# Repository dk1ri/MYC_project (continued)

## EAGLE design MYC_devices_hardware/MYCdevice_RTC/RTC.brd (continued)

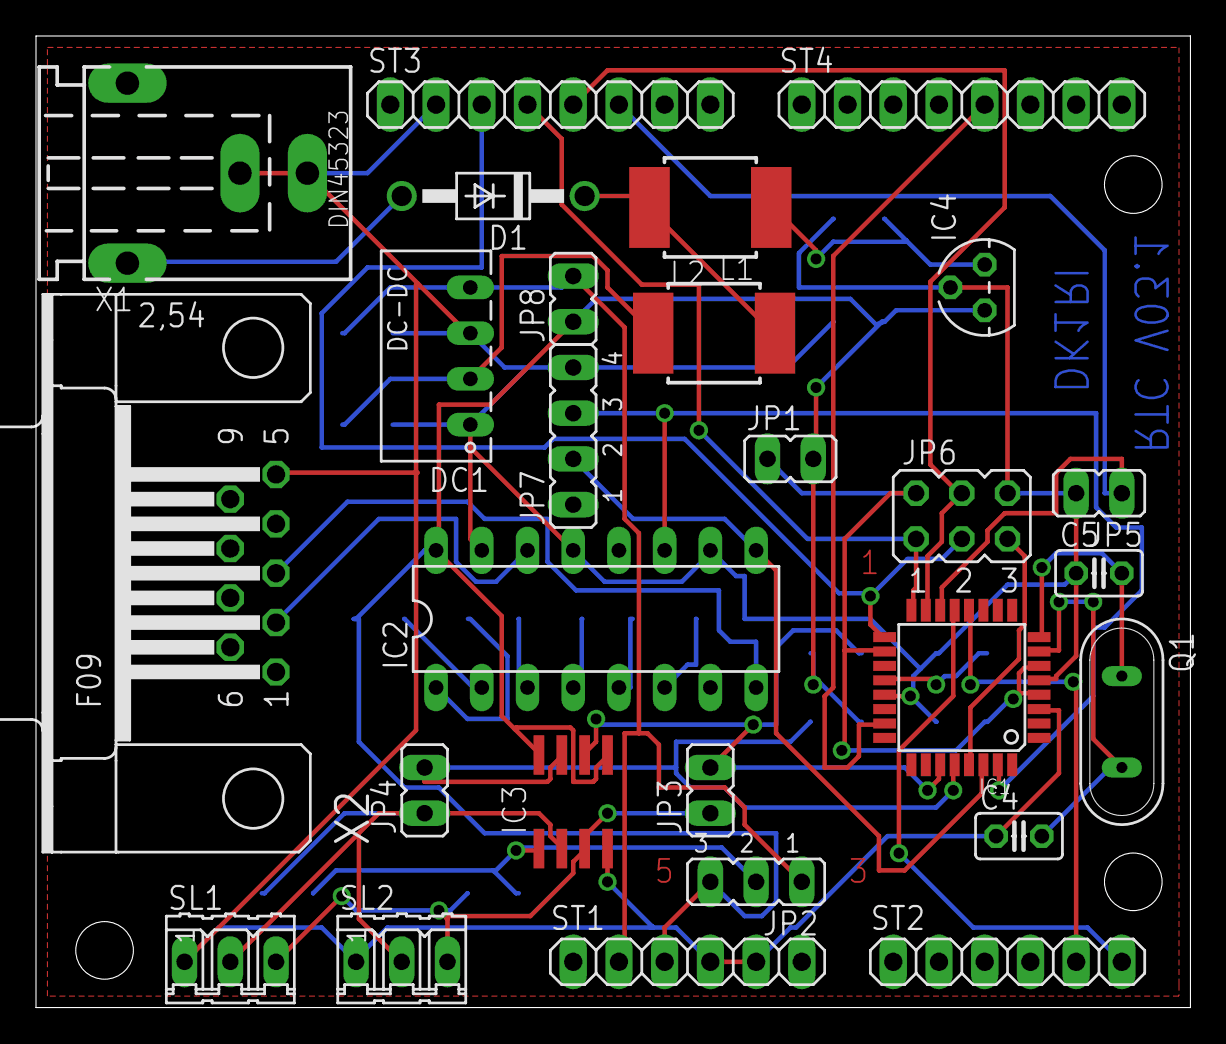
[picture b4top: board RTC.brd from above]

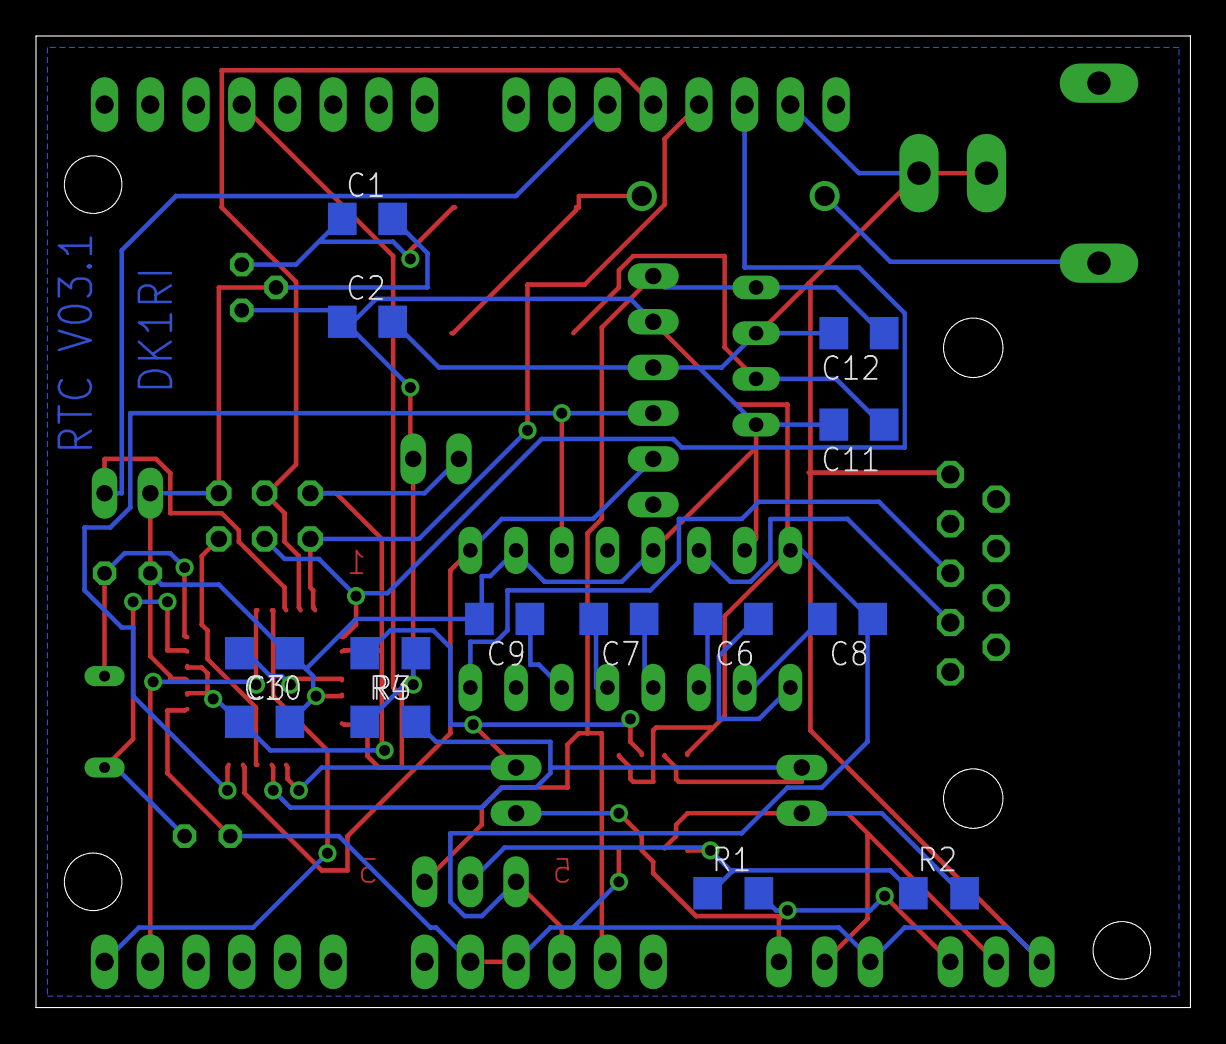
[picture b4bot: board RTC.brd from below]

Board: 2 copper layers, 64.1 x 54.0 mm, 41 parts (14 on the bottom side), 34 nets.

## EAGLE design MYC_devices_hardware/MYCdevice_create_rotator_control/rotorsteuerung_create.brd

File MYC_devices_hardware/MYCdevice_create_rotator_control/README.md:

# MYC Interface a Create RC5A Rotator

This is a device, which understand the MYC protocol via I2C and control a antenna rotator.

The board is designed to fit into the control box

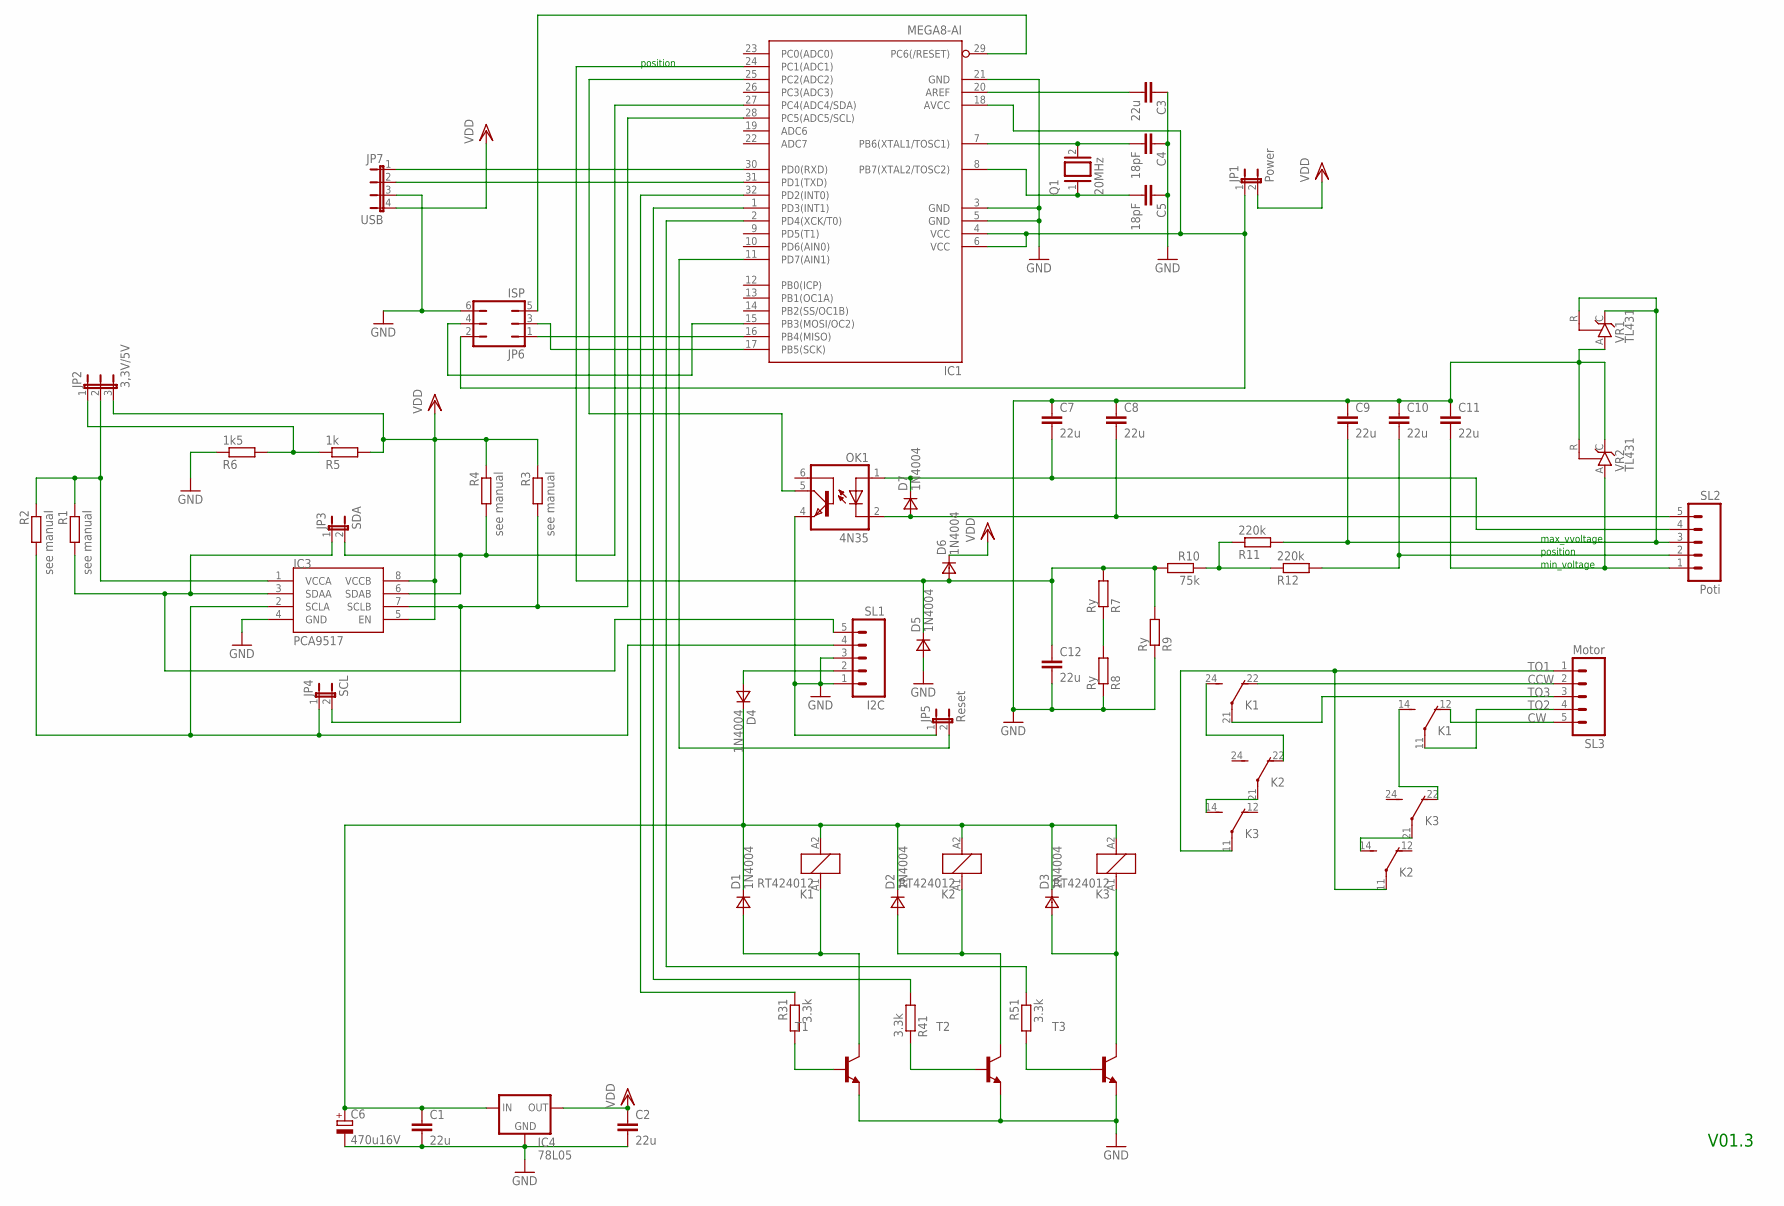
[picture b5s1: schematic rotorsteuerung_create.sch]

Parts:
C1, C2, C3, C7, C8, C9, C10, C11, C12: 22u; C1206
C4, C5: 18pF; C025-024X044
C6: 470u16V; E5-10,5
D1, D2, D3, D4, D5, D6, D7: 1N4004; E2LINE
IC1: MEGA8-AI; TQFP32-08
IC3: PCA9517; SO-08
IC4: 78L05; 78LXX
JP1: Power; JP1
JP2: 3,3V/5V; JP2
JP3: SDA; JP1
JP4: SCL; JP1
JP5: Reset; JP1
JP6: ISP; JP3Q
JP7: USB; JP4
K1, K2, K3: RT424012; RT2C/O
OK1: 4N35; DIL06
Q1: 20MHz; QS
R1, R2: see manual; M1206
R3, R4: see manual; R1206
R5: 1k; R1206
R6: 1k5; R1206
R7, R8, R9: Ry; 0204/7
R10: 75k; 0204/7
R11, R12: 220k; 0204/7
R31, R41, R51: 3.3k; R1206
SL1: I2C; 05P
SL2: Poti; 05P
SL3: Motor; 05P
T1, T2, T3: BC817-16-NPN-SOT23-BEC; SOT23-BEC
VR1, VR2: TL431; TO92-CLP

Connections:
C7: C7.2, D7.1 (C), OK1.1 (A), SL2.4
C9: C9.2, R11.2, SL2.3, VR1.C, VR1.R
CCW: K1.22 (O), SL3.2
CW: K1.12 (O), SL3.5
GND: C1.2, C2.2, C3.1, C4.1, C5.1, C6.-, C7.1, C8.1, C9.1, C10.1, C11.1, C12.2, D5.2 (A), IC1.3 (GND), IC1.5 (GND), IC1.21 (GND), IC3.4 (GND), IC4.GND, JP5.1, JP6.6, JP7.3, OK1.4 (EMI), R6.1, R8.1, R9.1, SL1.1, SL1.3, T1.E, T2.E, T3.E, VR1.A, VR2.C, VR2.R
unnamed: IC1.27 (PC4(ADC4/SDA)), IC3.6 (SDAB), JP3.2, R4.2
unnamed: C8.2, D7.2 (A), OK1.2 (C), SL2.5
unnamed: C11.2, SL2.1, VR2.A
unnamed: D4.2 (A), SL1.2
unnamed: K1.24 (S), K2.22 (O)
unnamed: R7.1, R8.2
unnamed: IC1.16 (PB4(MISO)), JP6.1
unnamed: K1.14 (S), K3.22 (O)
unnamed: R10.1, R11.1, R12.1
unnamed: IC1.4 (VCC), IC1.6 (VCC), IC1.18 (AVCC), JP1.1, JP6.2
unnamed: K2.21, K3.14 (S)
unnamed: R41.1, T2.B
unnamed: IC1.2 (PD4(XCK/T0)), R51.1
unnamed: K2.14 (S), K3.21
unnamed: C12.1, D5.1 (C), D6.2 (A), IC1.24 (PC1(ADC1)), R7.2, R9.2, R10.2
unnamed: JP2.1, R5.1, R6.2
unnamed: C4.2, IC1.7 (PB6(XTAL1/TOSC1)), Q1.2
unnamed: IC1.17 (PB5(SCK)), JP6.3
unnamed: IC1.1 (PD3(INT1)), R41.2
unnamed: IC1.25 (PC2(ADC2)), OK1.5 (COL)
unnamed: IC3.3 (SDAA), JP3.1, R1.2, SL1.5
unnamed: C1.1, C6.+, D1.1 (C), D2.1 (C), D3.1 (C), D4.1 (C), IC4.IN, K1.A2 (2), K2.A2 (2), K3.A2 (2)
unnamed: IC1.11 (PD7(AIN1)), JP5.2
unnamed: IC3.2 (SCLA), JP4.1, R2.2, SL1.4
unnamed: C10.2, R12.2, SL2.2
unnamed: IC3.1 (VCCA), JP2.2, R1.1, R2.1
unnamed: IC1.30 (PD0(RXD)), JP7.1
unnamed: IC1.15 (PB3(MOSI/OC2)), JP6.4
unnamed: IC1.31 (PD1(TXD)), JP7.2
unnamed: IC1.32 (PD2(INT0)), R31.1
unnamed: R31.2, T1.B
unnamed: C3.2, IC1.20 (AREF)
unnamed: R51.2, T3.B
unnamed: C5.2, IC1.8 (PB7(XTAL2/TOSC2)), Q1.1
unnamed: IC1.29 (PC6(/RESET)), JP6.5
unnamed: D1.2 (A), K1.A1 (1), T1.C
unnamed: D2.2 (A), K2.A1 (1), T2.C
unnamed: D3.2 (A), K3.A1 (1), T3.C
unnamed: IC1.28 (PC5(ADC5/SCL)), IC3.7 (SCLB), JP4.2, R3.2
TO1: K2.11, K3.11, SL3.1
TO2: K1.11, SL3.4
TO3: K1.21, SL3.3
VDD: C2.1, D6.1 (C), IC3.5 (EN), IC3.8 (VCCB), IC4.OUT, JP1.2, JP2.3, JP7.4, R3.1, R4.1, R5.2

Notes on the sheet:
V01.3
max_vvoltage
min_voltage
position

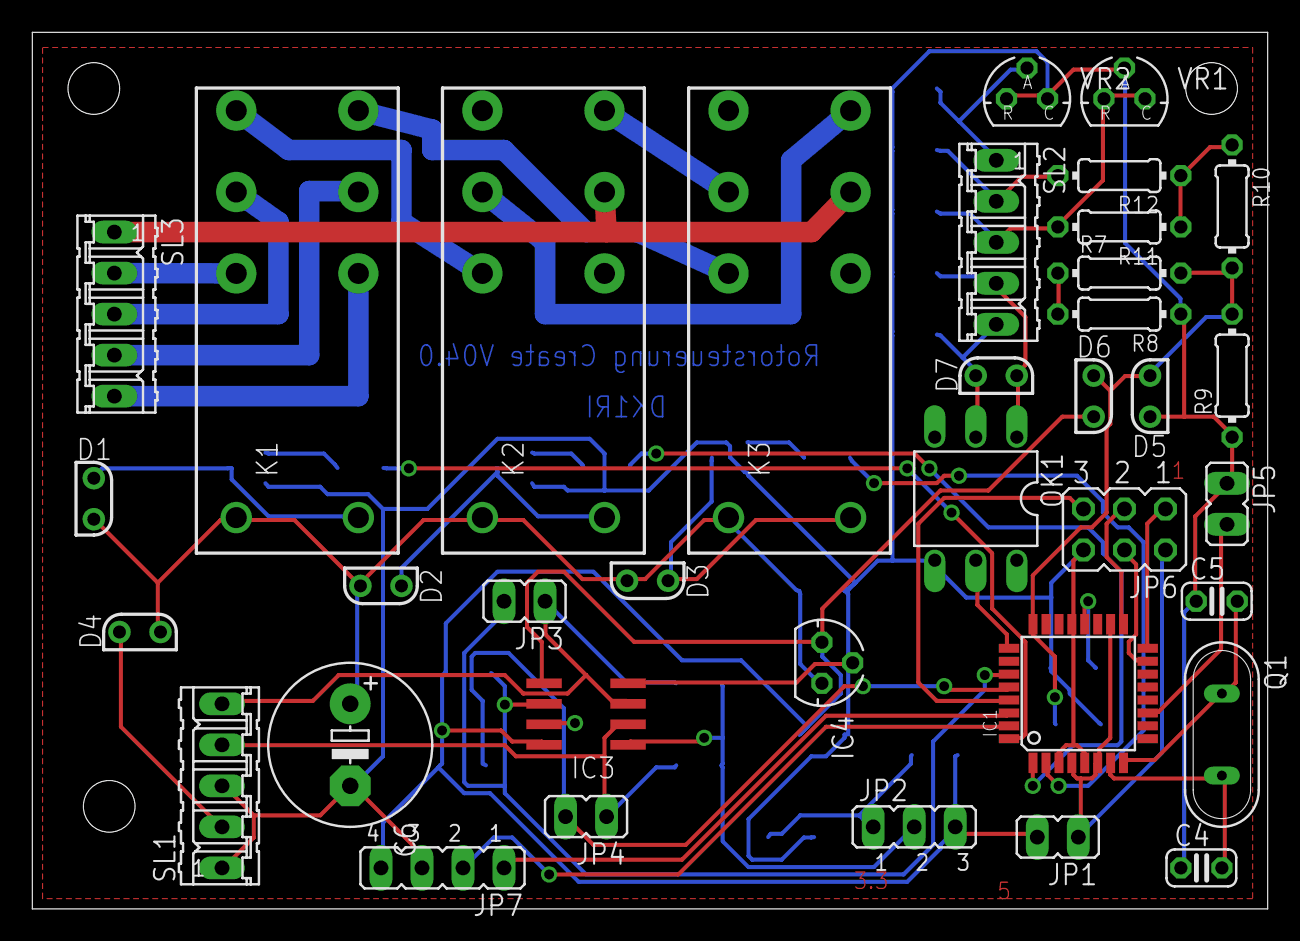
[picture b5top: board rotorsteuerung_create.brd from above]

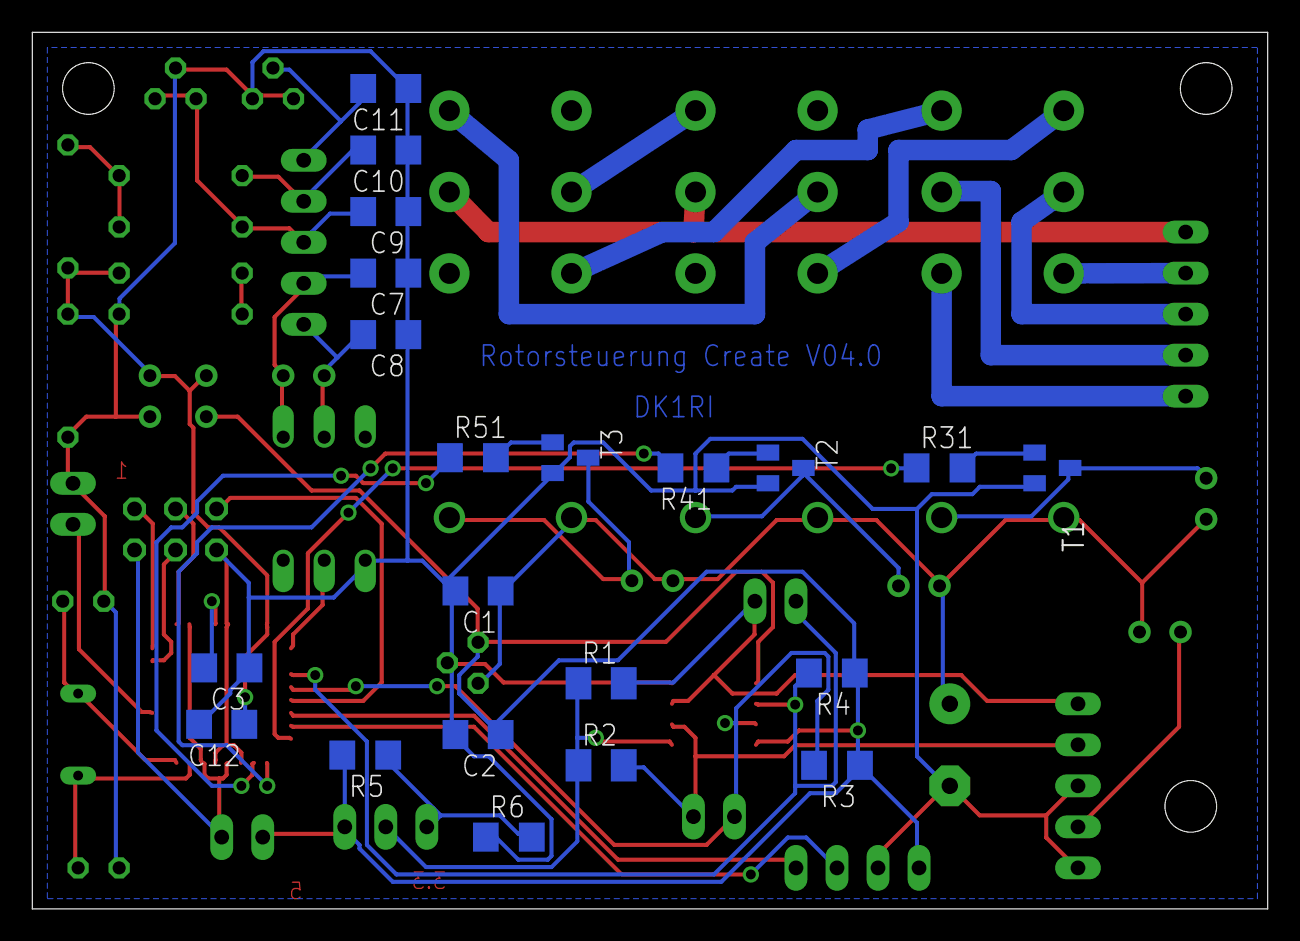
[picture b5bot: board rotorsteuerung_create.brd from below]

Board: 2 copper layers, 76.5 x 54.3 mm, 57 parts (21 on the bottom side), 48 nets.

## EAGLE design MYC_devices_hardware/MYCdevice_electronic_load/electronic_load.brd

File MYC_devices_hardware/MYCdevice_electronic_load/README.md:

# MYC electronic load
This is a device, which understand the MYC protocol via I2C or RS232/USB and works as a resistor, which can handle 90V, 210A or 350W (with 7 FETS IRFP150)

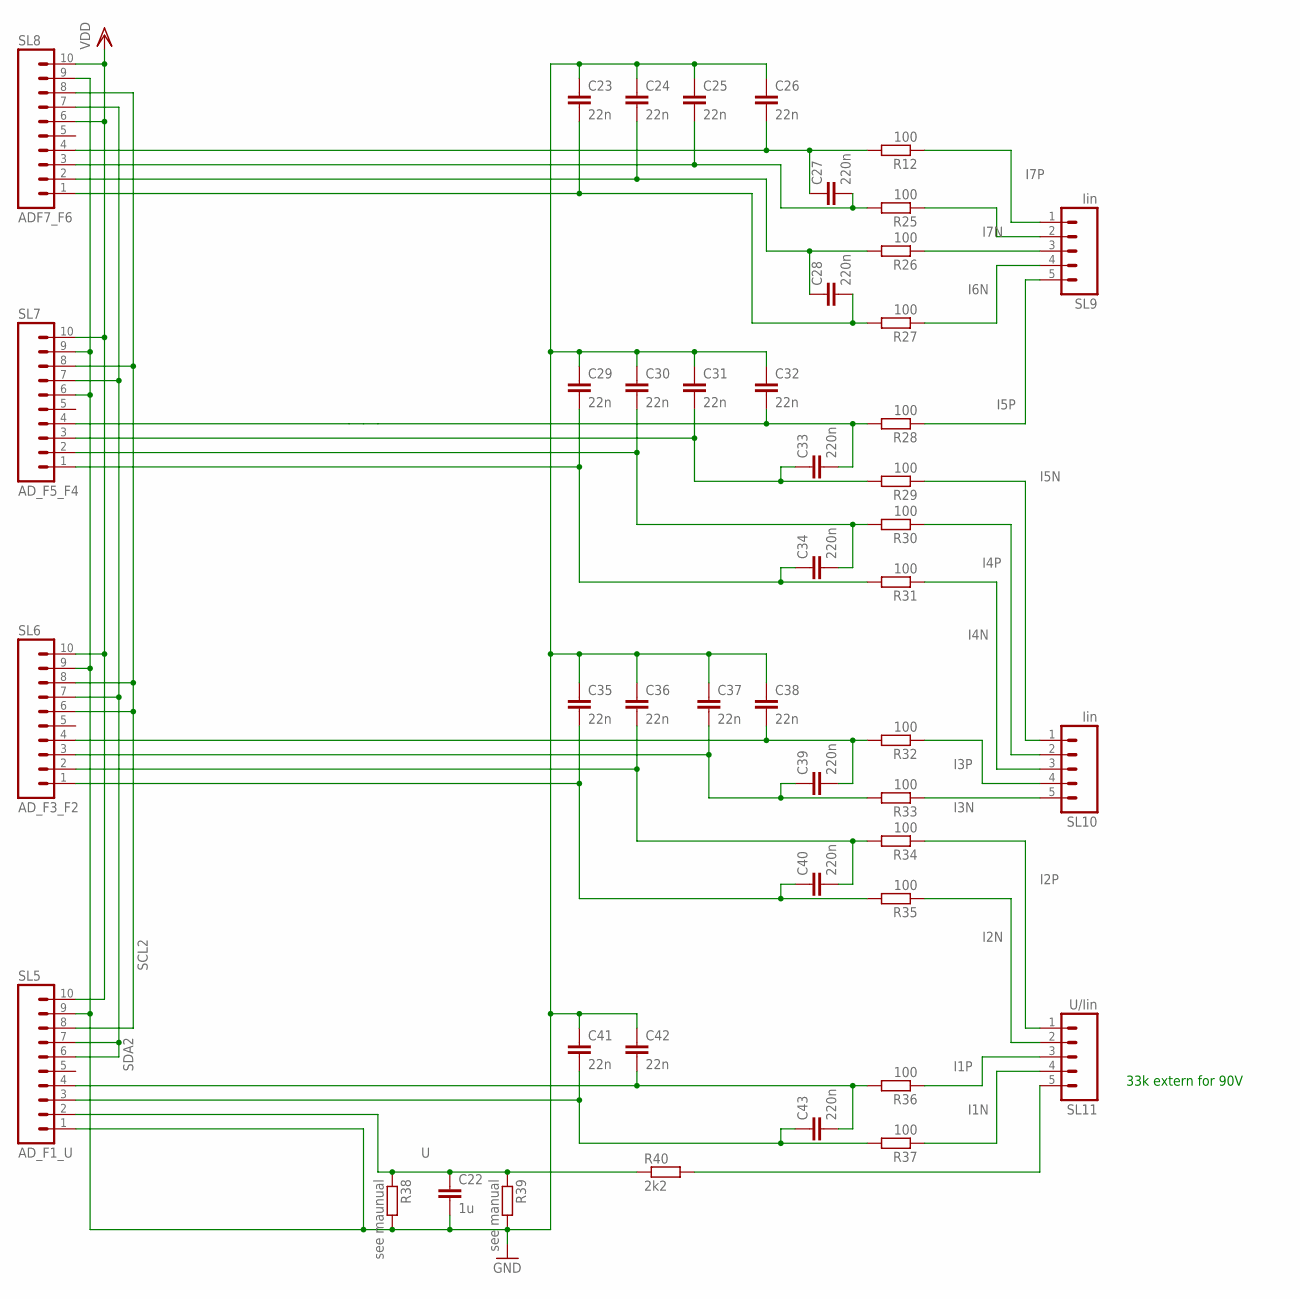
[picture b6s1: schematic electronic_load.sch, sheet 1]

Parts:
C22: 1u; C1206
C23, C24, C25, C26, C29, C30, C31, C32, C35, C36, C37, C38, C41, C42: 22n; C1206
C27, C28, C33, C34, C39, C40, C43: 220n; C1206
R12, R25, R26, R27, R28, R29, R30, R31, R32, R33, R34, R35, R36, R37: 100; R1206
R38: see maunual; R1206
R39: see manual; R1206
R40: 2k2; R1206
SL5: AD_F1_U; 10P
SL6: AD_F3_F2; 10P
SL7: AD_F5_F4; 10P
SL8: ADF7_F6; 10P
SL9, SL10: Iin; 05P
SL11: U/Iin; 05P

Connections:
GND: C22.2, C23.1, C24.1, C25.1, C26.1, C29.1, C30.1, C31.1, C32.1, C35.1, C36.1, C37.1, C38.1, C41.1, C42.1, R38.2, R39.2, SL5.1, SL5.9, SL6.9, SL7.6, SL7.9, SL8.9; also elsewhere on the board
I1N: R37.1, SL11.4
I1P: R36.1, SL11.3
I2N: R35.1, SL11.2
I2P: R34.1, SL11.1
I3N: R33.1, SL10.5
I3P: R32.1, SL10.4
I4N: R31.1, SL10.3
I4P: R30.1, SL10.2
I5N: R29.1, SL10.1
I5P: R28.1, SL9.5
I6N: R27.1, SL9.4
I6P: R26.1, SL9.3
I7N: R25.1, SL9.2
I7P: R12.1, SL9.1
unnamed: C26.2, C27.1, R12.2, SL8.4
unnamed: C32.2, C33.2, R28.2, SL7.4
unnamed: R40.2, SL11.5
unnamed: C31.2, C33.1, R29.2, SL7.3
unnamed: C30.2, C34.2, R30.2, SL7.2
unnamed: C29.2, C34.1, R31.2, SL7.1
unnamed: C38.2, C39.2, R32.2, SL6.4
unnamed: C37.2, C39.1, R33.2, SL6.3
unnamed: C36.2, C40.2, R34.2, SL6.2
unnamed: C24.2, C28.1, R26.2, SL8.2
unnamed: C25.2, C27.2, R25.2, SL8.3
unnamed: C35.2, C40.1, R35.2, SL6.1
unnamed: C23.2, C28.2, R27.2, SL8.1
unnamed: C42.2, C43.2, R36.2, SL5.4
unnamed: C41.2, C43.1, R37.2, SL5.3
SCL2: SL5.8, SL6.6, SL6.8, SL7.8, SL8.8; also elsewhere on the board
SDA2: SL5.6, SL5.7, SL6.7, SL7.7, SL8.7; also elsewhere on the board
U: C22.1, R38.1, R39.1, R40.1, SL5.2
VDD: SL5.10, SL6.10, SL7.10, SL8.6, SL8.10; also elsewhere on the board

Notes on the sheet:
33k extern for 90V

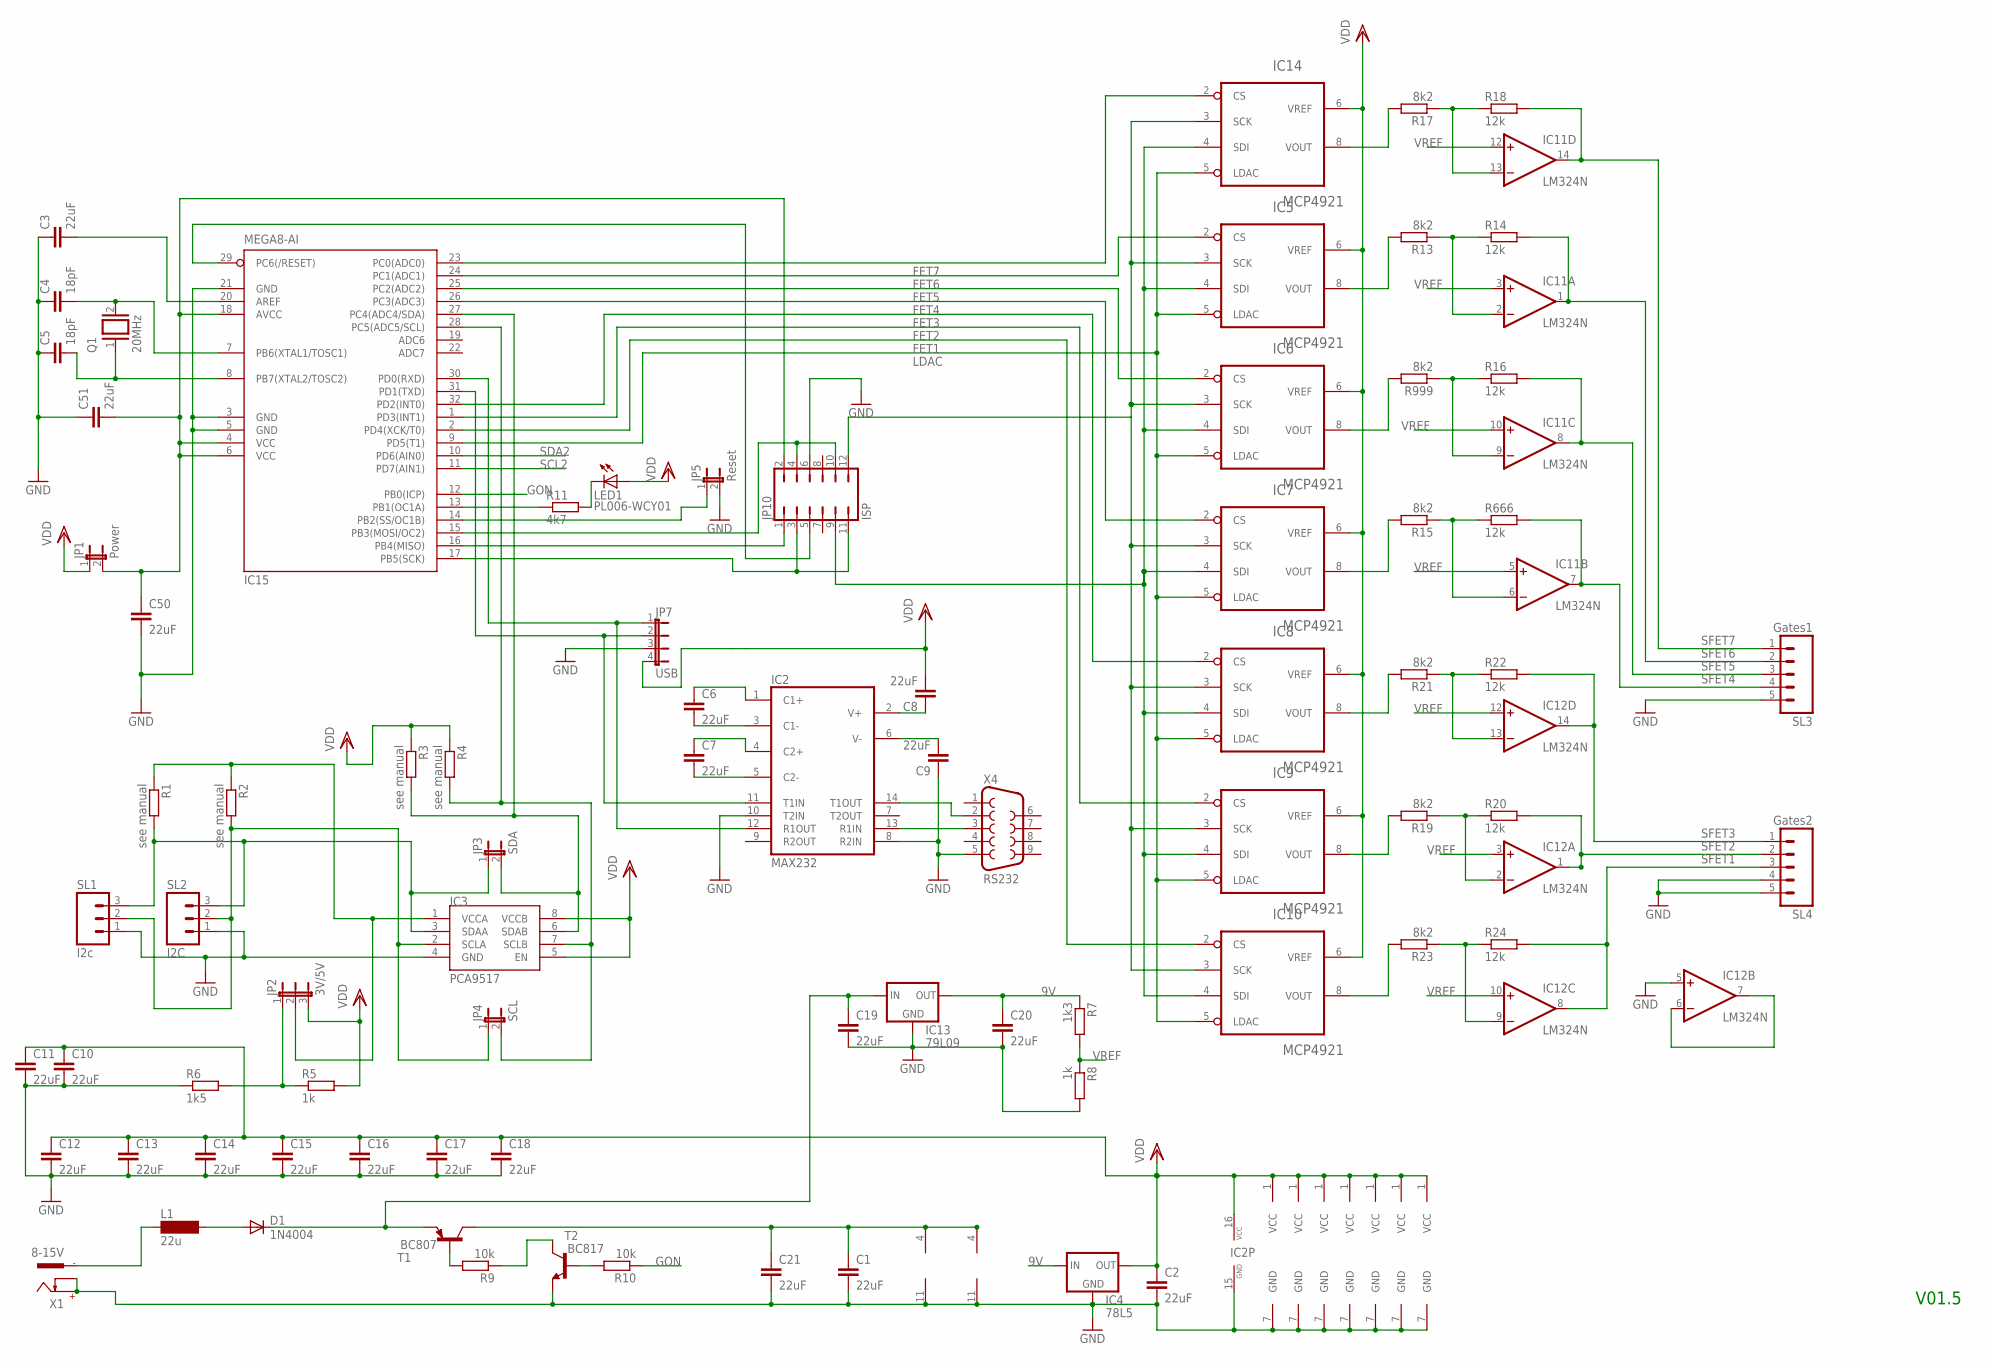
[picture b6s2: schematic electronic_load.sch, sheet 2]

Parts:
C1, C2, C3, C6, C7, C8, C9, C10, C11, C12, C13, C14, C15, C16, C17, C18, C19, C20, C21, C50, C51: 22uF; C1206
C4, C5: 18pF; C025-025X050
D1: 1N4004; DO41-10
IC2: MAX232; DIL16
IC3: PCA9517; SO-08
IC4: 78L5; 78LXX
IC5, IC6, IC7, IC8, IC9, IC10, IC14: MCP4921; DIL08
IC11, IC12: LM324N; DIL14
IC13: 79L09; 78LXX
IC15: MEGA8-AI; TQFP32-08
JP1: Power; JP1
JP2: 3V/5V; JP2
JP3: SDA; JP1
JP4: SCL; JP1
JP5: Reset; JP1
JP7: USB; JP4
JP10: ISP; JP6Q
L1: 22u; MS85
LED1: PL006-WCY01; SOT23
Q1: 20MHz; QS
R1, R2, R3, R4: see manual; R1206
R5, R8: 1k; R1206
R6: 1k5; R1206
R7: 1k3; R1206
R9, R10: 10k; R1206
R11: 4k7; R1206
R13, R15, R17, R19, R21, R23, R999: 8k2; R1206
R14, R16, R18, R20, R22, R24, R666: 12k; R1206
SL1: I2c; 03P
SL2: I2C; 03P
SL3: Gates1; 05P
SL4: Gates2; 05P
T1: BC807; SOT23-BEC
T2: BC817; SOT23-BEC
X1: 8-15V; 737992-5
X4: RS232; F09H

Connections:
9V: C20.1, IC4.IN, IC13.OUT, R7.1
C13: C6.1, IC2.1 (C1+)
FET1: IC10.2 (CS), IC15.2 (PD4(XCK/T0))
FET2: IC9.2 (CS), IC15.1 (PD3(INT1))
FET3: IC8.2 (CS), IC15.32 (PD2(INT0))
FET4: IC7.2 (CS), IC15.26 (PC3(ADC3))
FET5: IC6.2 (CS), IC15.25 (PC2(ADC2))
FET6: IC5.2 (CS), IC15.24 (PC1(ADC1))
FET7: IC14.2 (CS), IC15.23 (PC0(ADC0))
GND: C1.2, C2.2, C3.1, C4.1, C5.1, C9.1, C10.2, C11.2, C12.2, C13.2, C14.2, C15.2, C16.2, C17.2, C18.2, C19.2, C20.2, C21.2, C50.2, C51.1, IC2.8 (R2IN), IC2.10 (T2IN), IC2.15 (GND), IC3.4 (GND), IC4.GND, IC5.7 (GND), IC6.7 (GND), IC7.7 (GND), IC8.7 (GND), IC9.7 (GND), IC10.7 (GND), IC11.11 (V-), IC12.5 (+IN), IC12.11 (V-), IC13.GND, IC14.7 (GND), IC15.3 (GND), IC15.5 (GND), IC15.21 (GND), JP5.2, JP7.3, JP10.6, R6.1, R8.2, SL1.1, SL2.1, SL3.5, SL4.4, SL4.5, T2.E, X1.+, X1.K, X4.5; also elsewhere on the board
GON: IC15.12 (PB0(ICP)), R10.1
LDAC: IC5.5 (LDAC), IC6.5 (LDAC), IC7.5 (LDAC), IC8.5 (LDAC), IC9.5 (LDAC), IC10.5 (LDAC), IC14.5 (LDAC), IC15.9 (PD5(T1))
unnamed: C7.2, IC2.5 (C2-)
unnamed: C50.1, C51.2, IC15.4 (VCC), IC15.6 (VCC), IC15.18 (AVCC), JP1.2, JP10.2
unnamed: IC3.3 (SDAA), JP3.1, R1.2, SL1.3, SL2.3
unnamed: IC2.11 (T1IN), IC15.31 (PD1(TXD)), JP7.2
unnamed: L1.1, X1.-1
unnamed: IC2.13 (R1IN), X4.3
unnamed: IC6.8 (VOUT), R999.2
unnamed: C5.2, IC15.8 (PB7(XTAL2/TOSC2)), Q1.1
unnamed: D1.A, L1.2
unnamed: C7.1, IC2.4 (C2+)
unnamed: C6.2, IC2.3 (C1-)
unnamed: IC15.16 (PB4(MISO)), JP10.1
unnamed: C8.1, IC2.2 (V+)
unnamed: C9.2, IC2.6 (V-)
unnamed: IC15.29 (PC6(/RESET)), JP10.5
unnamed: C4.2, IC15.7 (PB6(XTAL1/TOSC1)), Q1.2
unnamed: IC5.4 (SDI), IC6.4 (SDI), IC7.4 (SDI), IC8.4 (SDI), IC9.4 (SDI), IC10.4 (SDI), IC14.4 (SDI), JP10.9
unnamed: IC14.8 (VOUT), R17.2
unnamed: IC3.2 (SCLA), JP4.1, R2.2, SL1.2, SL2.2
unnamed: IC15.15 (PB3(MOSI/OC2)), JP10.4, JP10.10
unnamed: IC9.8 (VOUT), R19.2
unnamed: IC8.8 (VOUT), R21.2
unnamed: IC5.3 (SCK), IC6.3 (SCK), IC7.3 (SCK), IC8.3 (SCK), IC9.3 (SCK), IC10.3 (SCK), IC14.3 (SCK), JP10.12
unnamed: IC5.8 (VOUT), R13.2
unnamed: IC2.14 (T1OUT), X4.2
unnamed: IC3.6 (SDAB), IC15.27 (PC4(ADC4/SDA)), JP3.2, R3.2
unnamed: IC11.13 (-IN), R17.1, R18.1
unnamed: IC15.14 (PB2(SS/OC1B)), JP5.1
unnamed: IC11.9 (-IN), R16.1, R999.1
unnamed: IC10.8 (VOUT), R23.2
unnamed: IC12.13 (-IN), R21.1, R22.1
unnamed: IC2.12 (R1OUT), IC15.30 (PD0(RXD)), JP7.1
unnamed: LED1.3 (C), R11.2
unnamed: IC15.17 (PB5(SCK)), JP10.3, JP10.11
unnamed: IC3.7 (SCLB), IC15.28 (PC5(ADC5/SCL)), JP4.2, R4.2
unnamed: JP2.1, R5.1, R6.2
unnamed: IC15.13 (PB1(OC1A)), R11.1
unnamed: IC7.8 (VOUT), R15.2
unnamed: C19.1, D1.C, IC13.IN, T1.E
unnamed: IC12.2 (-IN), R19.1, R20.1
unnamed: IC12.9 (-IN), R23.1, R24.1
unnamed: C1.1, C21.1, IC11.4 (V+), IC12.4 (V+), T1.C
unnamed: C3.2, IC15.20 (AREF)
unnamed: R9.2, T1.B
unnamed: IC3.1 (VCCA), JP2.2, R1.1, R2.1
unnamed: R9.1, T2.C
unnamed: R10.2, T2.B
unnamed: IC11.6 (-IN), R15.1, R666.1
unnamed: IC11.2 (-IN), R13.1, R14.1
unnamed: IC12.6 (-IN), IC12.7 (OUT)
SCL2: IC15.11 (PD7(AIN1)); also elsewhere on the board
SDA2: IC15.10 (PD6(AIN0)); also elsewhere on the board
SFET1: IC12.8 (OUT), R24.2, SL4.3
SFET2: IC12.1 (OUT), R20.2, SL4.2
SFET3: IC12.14 (OUT), R22.2, SL4.1
SFET4: IC11.7 (OUT), R666.2, SL3.4
SFET5: IC11.8 (OUT), R16.2, SL3.3
SFET6: IC11.1 (OUT), R14.2, SL3.2
SFET7: IC11.14 (OUT), R18.2, SL3.1
VDD: C2.1, C8.2, C10.1, C11.1, C12.1, C13.1, C14.1, C15.1, C16.1, C17.1, C18.1, IC2.16 (VCC), IC3.5 (EN), IC3.8 (VCCB), IC4.OUT, IC5.1 (VCC), IC5.6 (VREF), IC6.1 (VCC), IC6.6 (VREF), IC7.1 (VCC), IC7.6 (VREF), IC8.1 (VCC), IC8.6 (VREF), IC9.1 (VCC), IC9.6 (VREF), IC10.1 (VCC), IC10.6 (VREF), IC14.1 (VCC), IC14.6 (VREF), JP1.1, JP2.3, JP7.4, LED1.1 (A), R3.1, R4.1, R5.2; also elsewhere on the board
VREF: IC11.3 (+IN), IC11.5 (+IN), IC11.10 (+IN), IC11.12 (+IN), IC12.3 (+IN), IC12.10 (+IN), IC12.12 (+IN), R7.2, R8.1

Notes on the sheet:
V01.5

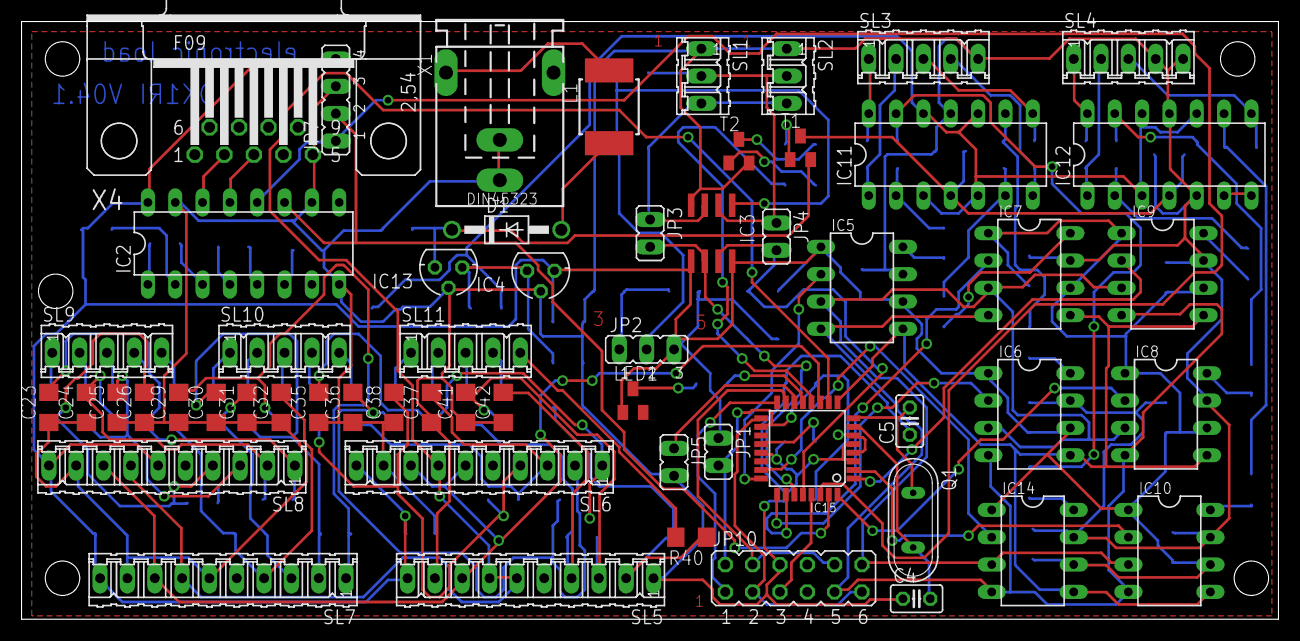
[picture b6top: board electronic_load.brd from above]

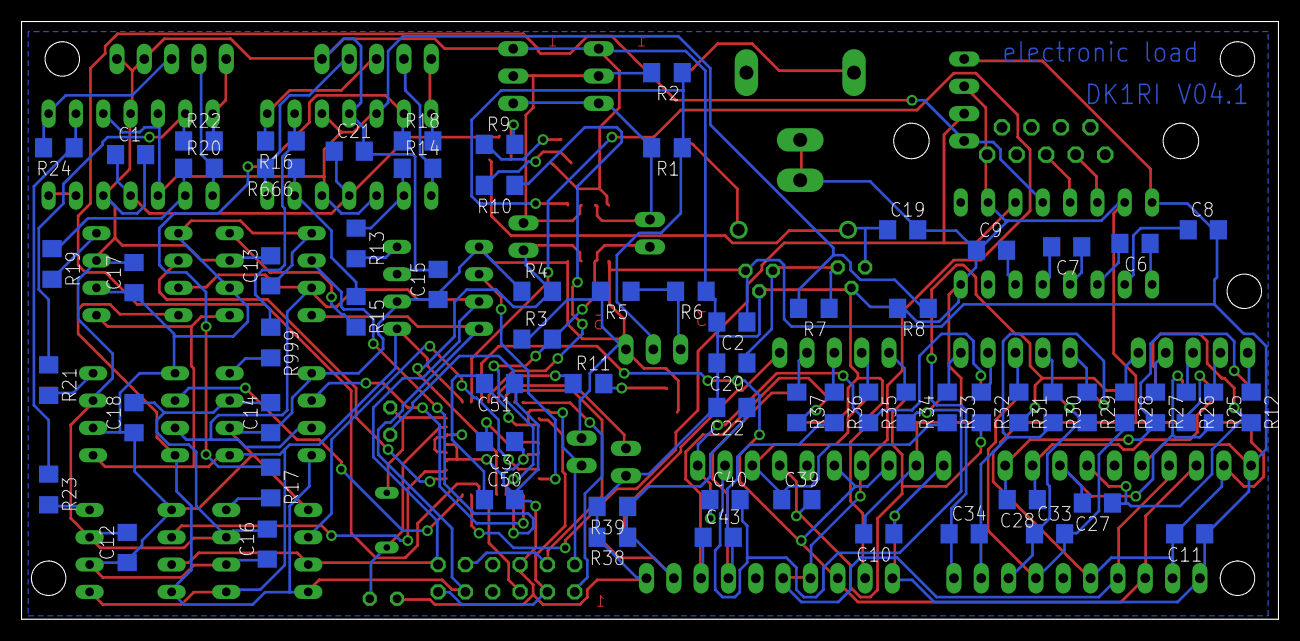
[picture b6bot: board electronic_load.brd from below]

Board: 2 copper layers, 116.8 x 55.5 mm, 127 parts (70 on the bottom side), 103 nets.
